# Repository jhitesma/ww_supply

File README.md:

# Wall wart ±12V power supply

## Untested! Assume nothing has been checked and nothing works!

This is a power supply based on the [MFOS wall wart supply](http://musicfromouterspace.com/analogsynth_new/WALLWARTSUPPLY/WALLWARTSUPPLY.php). Differences are:

* Added polyfuses
* Added LEDs
* Input is a pluggable terminal block, with another one for daisy chaining
* Output is a (non pluggable) terminal block
* Regulators are vertical, with space for Tayda A-5093 heat sinks
* Board is shorter and wider (100 x 61 mm) to keep fabbing price low

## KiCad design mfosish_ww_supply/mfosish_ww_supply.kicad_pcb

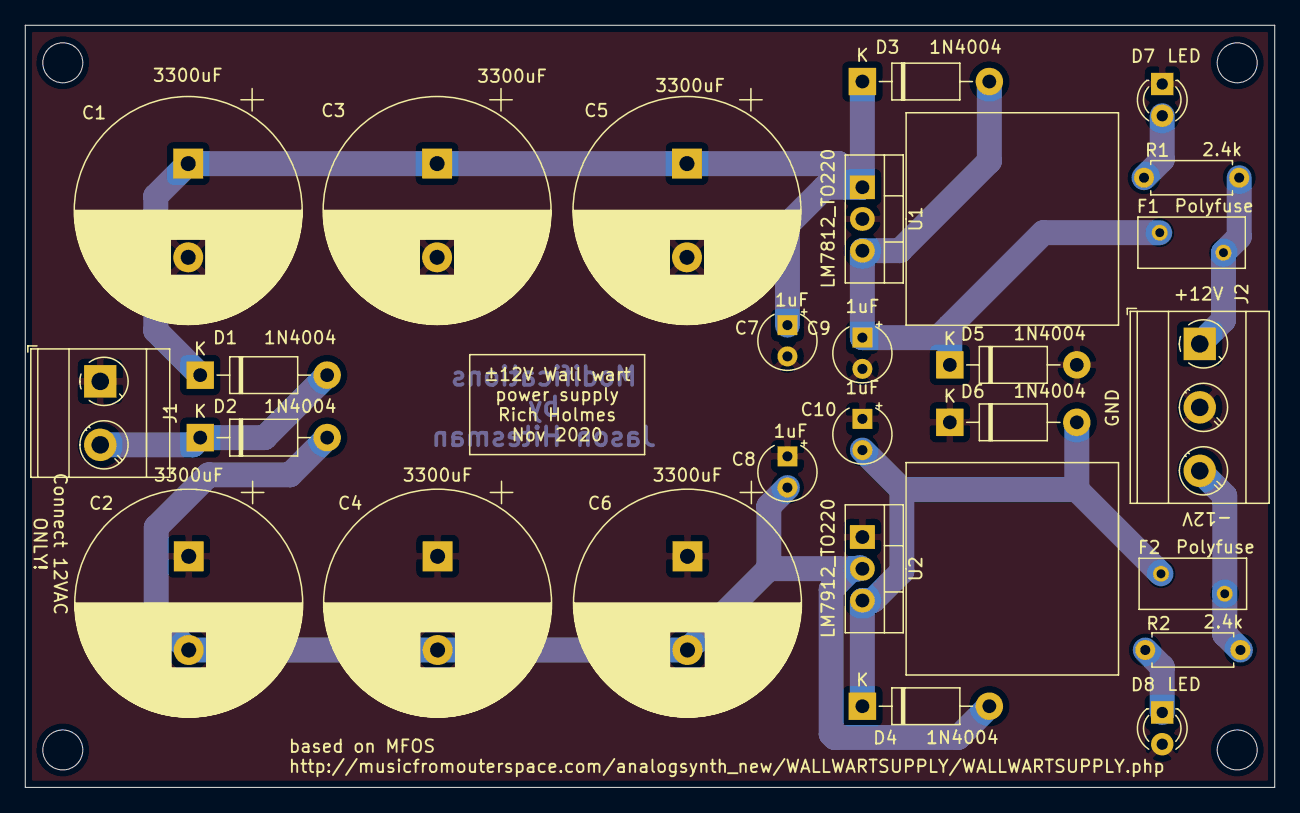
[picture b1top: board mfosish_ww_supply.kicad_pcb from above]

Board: 2 copper layers, 100.0 x 61.0 mm, 26 parts (0 on the bottom side), 10 nets.

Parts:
C1, C2, C3, C4, C5, C6: 3300uF; CP_Radial_D18.0mm_P7.50mm
C7, C8, C9, C10: 1uF; CP_Radial_Tantal_D4.5mm_P2.50mm
D1, D2, D3, D4, D5, D6: 1N4004; D_DO-41_SOD81_P10.16mm_Horizontal
D7, D8: LED; LED_D3.0mm
F1, F2: Polyfuse; Fuse_BelFuse_0ZRE0005FF_L8.3mm_W3.8mm
J1: Conn_01x02; TerminalBlock_MetzConnect_Type073_RT02602HBLU_1x02_P5.08mm_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
J2: Conn_01x03; TerminalBlock_MetzConnect_Type073_RT02603HBLU_1x03_P5.08mm_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
R1, R2: 2.4k; R_Axial_DIN0207_L6.3mm_D2.5mm_P7.62mm_Horizontal
U1: LM7812_TO220; TO-220-3_Vertical
U2: LM7912_TO220; TO-220-3_Vertical

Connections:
+12V: F1.1, J2.1, R1.2
-12V: F2.1, J2.3, R2.2
GND: C1.2, C2.1, C3.2, C4.1, C5.2, C6.1, C7.2, C8.1, C9.2, C10.1, D5.2, D6.1, D7.1, D8.2, J1.1, J2.2, U1.2, U2.1
unnamed: C1.1, C3.1, C5.1, C7.1, D1.1, D3.1, U1.1
unnamed: C2.2, C4.2, C6.2, C8.2, D2.2, D4.2, U2.2
unnamed: C9.1, D3.2, D5.1, F1.2, U1.3
unnamed: C10.2, D4.1, D6.2, F2.2, U2.3
unnamed: D1.2, D2.1, J1.2
unnamed: D7.2, R1.1
unnamed: D8.1, R2.1

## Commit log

2020-11-17 Initial version
2020-11-17 Correct typo
2020-11-18 Modifications for DIY etching, only one AC connector and 3.81mm pitch connectors.
2020-11-19 Few more cleanups
    Repositioned D1/D2, Cleaned up labels, redid a few wonky traces
2020-11-19 Whoops, fix copper pours
2020-11-25 Switch connectors...add text
2020-11-25 Add interactive BOM
2020-11-25 PDF's for self-etching
